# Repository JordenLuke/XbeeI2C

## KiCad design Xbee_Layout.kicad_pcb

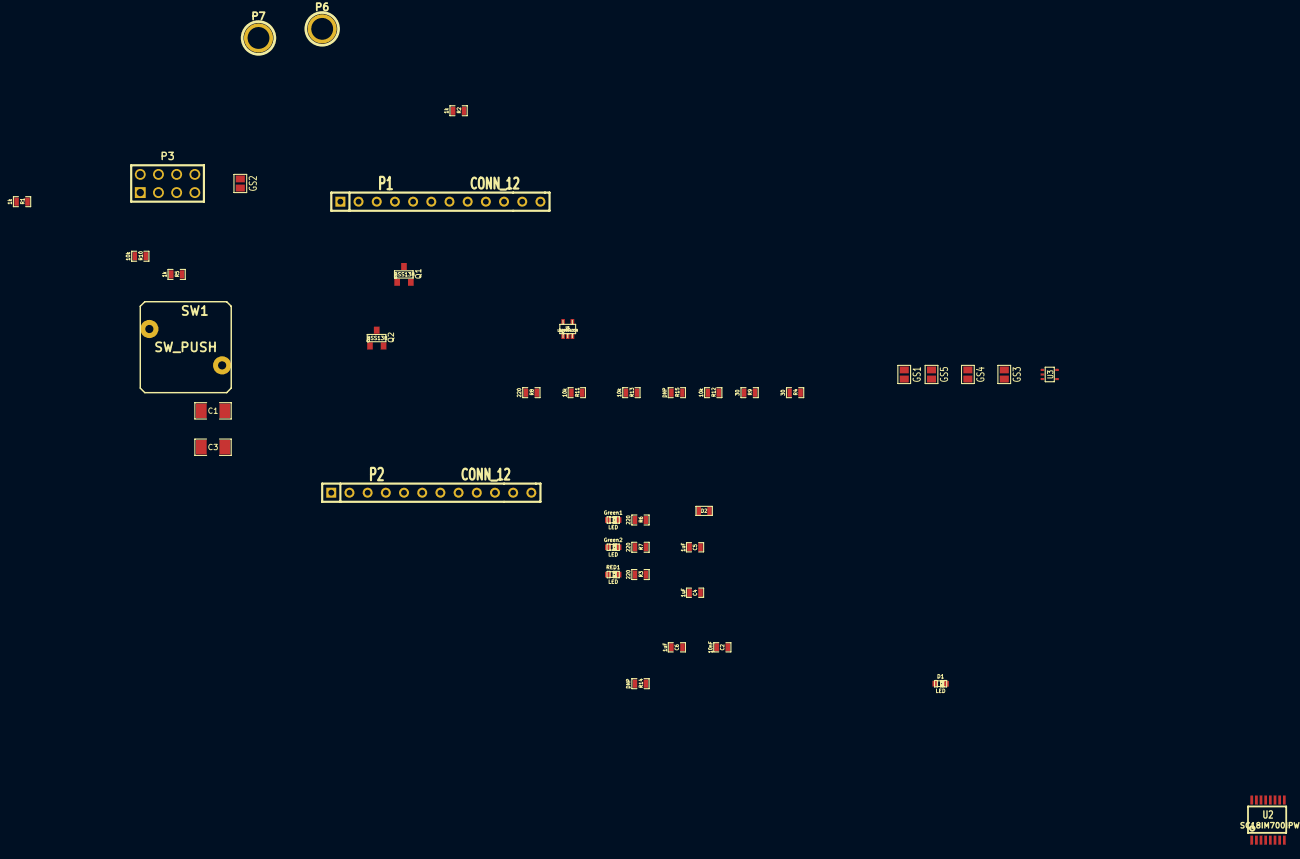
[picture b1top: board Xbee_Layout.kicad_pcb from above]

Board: 2 copper layers, 42 parts (0 on the bottom side), 34 nets, no tracks yet.

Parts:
C1, C3: 10uF; SM1206
C2: 10nF; SM0603_Capa
C4, C5, C6: 1uF; SM0603_Capa
D1: LED; LED-0603
D2: DIODE; SM0603
GS1, GS2, GS3, GS4, GS5: GS2
Green1, Green2: LED; LED-0603
P1, P2: CONN_12; SIL-12
P3: CONN_4X2; pin_array_4x2
P6: /RST; 1pin
P7: Vref; 1pin
Q1, Q2: BSS138; SOT23
R1, R2, R5: 1k; SM0603_Resistor
R3, R6, R7, R8: 220; SM0603_Resistor
R4, R9: 30; SM0603_Resistor
R10, R11, R12, R13: 10k; SM0603_Resistor
R14, R15: DNP; SM0603_Resistor
RED1: LED; LED-0603
SW1: SW_PUSH
U1: LD3985G33R; sot323-5
U2: SC18IM700IPW; TSSOP16
U3: XBEE; SOT353

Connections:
+3.3V: C4.1, C5.1, C6.1, Green1.1, Green2.1, Q1.1, Q2.1, R5.1, R10.1, R12.1, R14.1, RED1.1, U1.5, U2.12, U3.1
//CTS: GS4.2, P2.8
//RST: P6.1, U3.5
/CTS: GS4.1, Q2.2
/DO8: P2.9, U3.4
/GPIO0: P1.5, U2.1
/GPIO1: P1.6, U2.2
/GPIO2: P1.7, U2.5
/GPIO3: P1.8, U2.6
/GPIO4: P1.9, U2.15
/GPIO5: P1.10, U2.14
/GPIO6: P1.11, U2.11
/I2CREST: P1.3, SW1.1, U2.3
/RSSI: GS1.1, P2.11
/RxI: P3.1, P3.8
/RxI2C: GS2.2, P3.5, R4.2, R6.2
/RxXB: GS3.1, P3.4, R9.1
/SCL: P1.1, R2.2, U2.8
/SDA: P1.2, R1.2, U2.7
/Tx: P3.2, P3.7, Q1.2
/TxI2C: GS3.2, P3.3, R7.2, U2.10
/TxXB: GS2.1, P3.6, U3.2
/Vref: P7.1, R14.2, R15.1
/WAKE: P1.4, R5.2, U2.13
GND: C1.2, C2.2, C3.2, C4.2, C5.2, C6.2, R3.2, R8.2, R15.2, SW1.2, U1.2, U2.4
unnamed: D1.1, GS1.2
unnamed: R9.2, U3.3
unnamed: C2.1, U1.4
unnamed: D1.2, R8.1
unnamed: R3.1, RED1.2
unnamed: R4.1, U2.9
unnamed: Green2.2, R7.1
unnamed: Green1.2, R6.1
VCC: C1.1, D2.2, R11.1, R13.1, U1.1, U1.3

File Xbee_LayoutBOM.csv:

10nF,1,"C2",~,~
1uF,2,"C4 C5",~,~
10uF,2,"C1 C3",~,~
C,1,"C6",~,~
LED,4,"D1 Green1 Green2 RED1",~,~
DIODE,1,"D2",~,~
GS2,5,"GS1 GS2 GS3 GS4 GS5",~,~
CONN_12,2,"P1 P2",,
CONN_4X2,1,"P3",,,Molex,0901310764
LIPO,1,"P4",,
FTDI Breakout,1,"P5",,
/RST,1,"P6",~,~
Vref,1,"P7",~,~
BSS138,2,"Q1 Q2",SOT-23,~
30,2,"R4 R9",~,~
220,4,"R3 R6 R7 R8",~,~
1k,3,"R1 R2 R5",~,~
10k,4,"R10 R11 R12 R13",~,~
DNP,2,"R14 R15",~,~
SW_PUSH,1,"SW1",~,~
XBEE,1,"U3",,
LD3985G33R,1,"U1",TSOT-23-5,~
SC18IM700IPW,1,"U2",TSSOP-16,DOCUMENTATION

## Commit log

2014-08-11 :tada: Added .gitattributes & .gitignore files
2014-08-11 Add modules
    Rev OR 8/10/2014
2014-08-11 Added connectors and Jumpers
2014-08-12 Added Lib
    I added the Lib for the I2C chip for better compatiablity
2014-08-12 Tried to fix lib
2014-08-12 Tried to fix lib II
2014-08-12 Fixed lib III
2014-08-12 What the heck
2014-08-12 I dont kow
2014-08-12 Please Fix
2014-08-12 Added this
2014-08-12 One more try
2014-08-12 Fixing lib still
2014-08-12 Fixed everything i hope
2014-08-13 LEDs
    Added power LED and rx tx indicating LEDs between the I2C module and the
    XBee
2014-08-13 Reorganized stuff
2014-08-18 Almost finished
